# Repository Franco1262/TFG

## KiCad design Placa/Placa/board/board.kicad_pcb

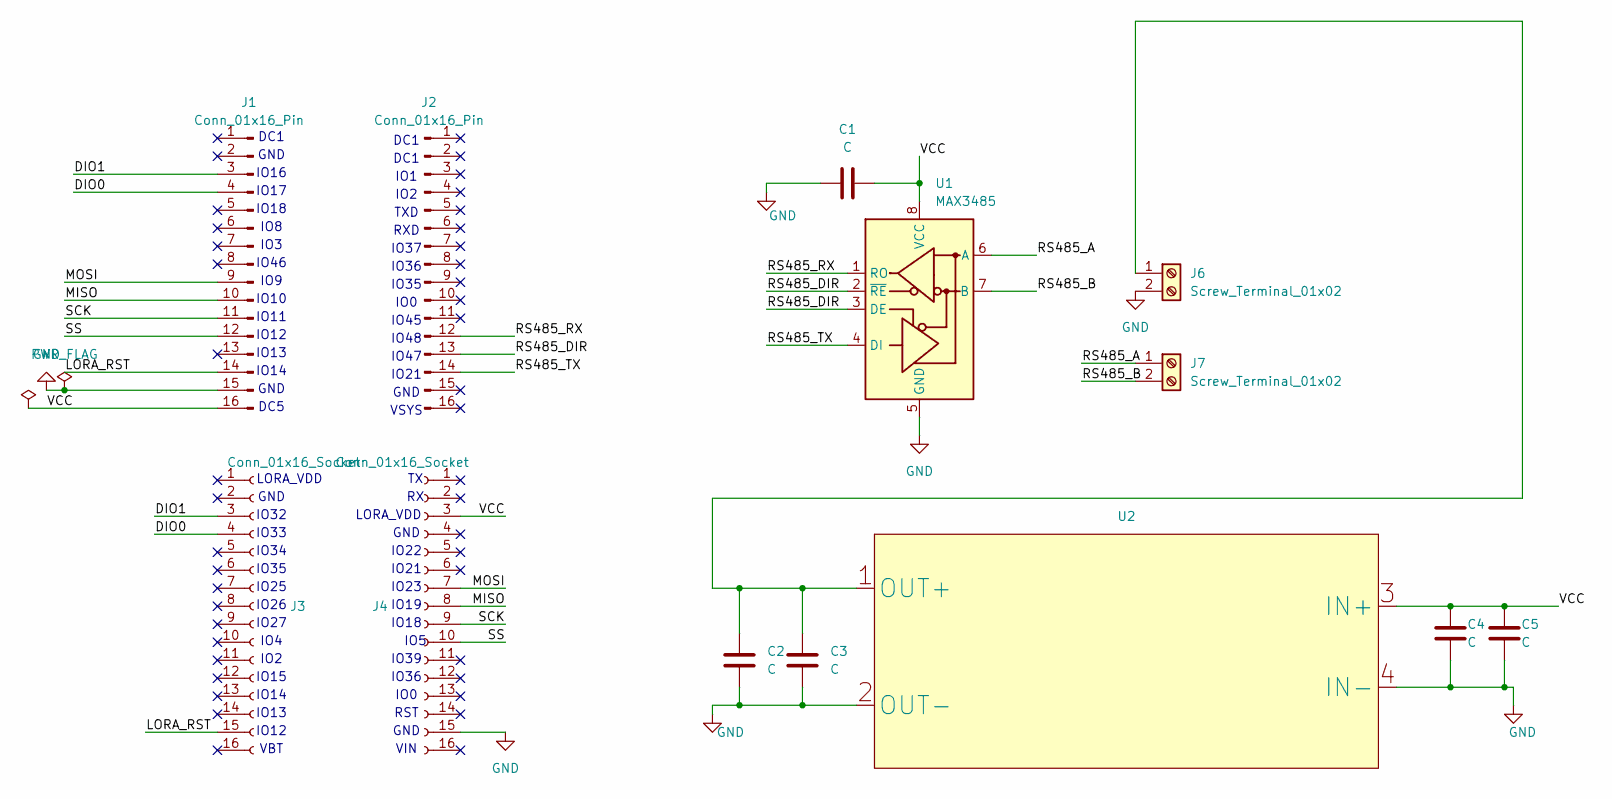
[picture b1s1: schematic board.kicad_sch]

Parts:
C1, C2, C3, C4, C5: C; C_Disc_D5.0mm_W2.5mm_P2.50mm
J1, J2: Conn_01x16_Pin; PinHeader_1x16_P2.54mm_Vertical
J3, J4: Conn_01x16_Socket; PinSocket_1x16_P2.54mm_Vertical
J6, J7: Screw_Terminal_01x02; TerminalBlock_Phoenix_MKDS-1,5-2-5.08_1x02_P5.08mm_Horizont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
U1: MAX3485; DIP-8_W7.62mm
U2: XL6019_Module; Module_XL6019

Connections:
/DIO0: J1.4, J3.4
/DIO1: J1.3, J3.3
/LORA_RST: J1.14, J3.15
/MISO: J1.10, J4.8
/MOSI: J1.9, J4.7
/RS485_A: J7.1, U1.6 (A)
/RS485_B: J7.2, U1.7 (B)
/RS485_DIR: J2.13, U1.2 (~RE), U1.3 (DE)
/RS485_RX: J2.12, U1.1 (RO)
/RS485_TX: J2.14, U1.4 (DI)
/SCK: J1.11, J4.9
/SS: J1.12, J4.10
/VCC: C1.2, C4.2, C5.2, J1.16, J4.3, U1.8 (VCC), U2.3 (IN+)
GND: C1.1, C2.1, C3.1, C4.1, C5.1, J1.15, J4.15, J6.2, U1.5 (GND), U2.2 (OUT-), U2.4 (IN-)
unnamed: C2.2, C3.2, J6.1, U2.1 (OUT+)

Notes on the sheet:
IO2
IO26
RXD
IO13
IO36
RST
IO48
LORA_VDD
GND
IO35
IO32
IO21
IO16
IO17
IO23
DC5
IO18
IO14
IO19
IO5
DC1
IO13
IO9
IO11
VSYS
IO1
IO15
IO34
IO25
GND
IO0
IO12
IO3
IO27
VBT
IO39
TXD
IO37
DC1
IO46

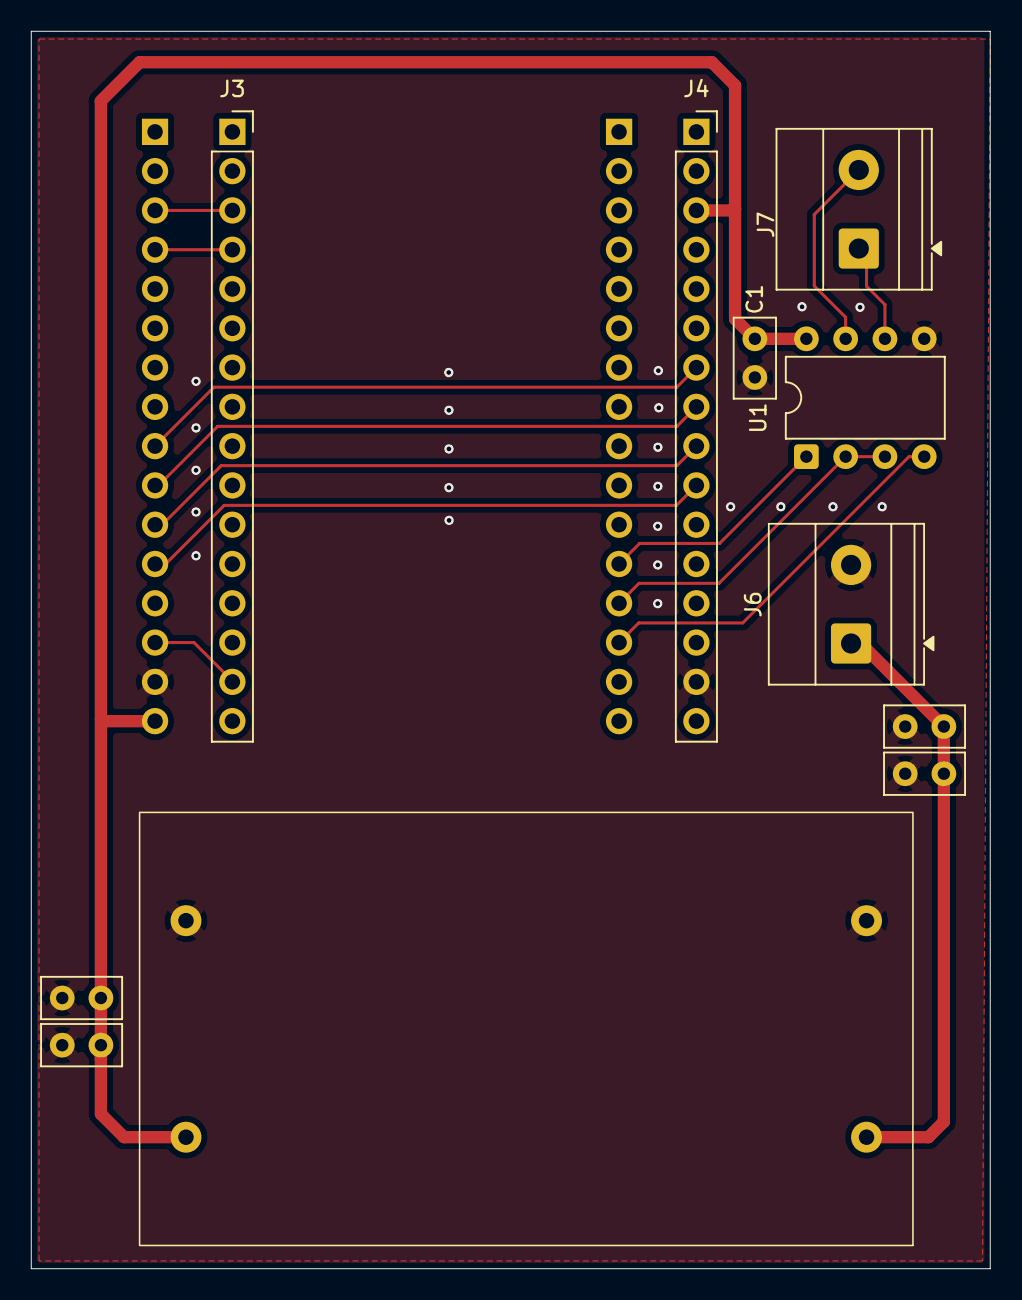
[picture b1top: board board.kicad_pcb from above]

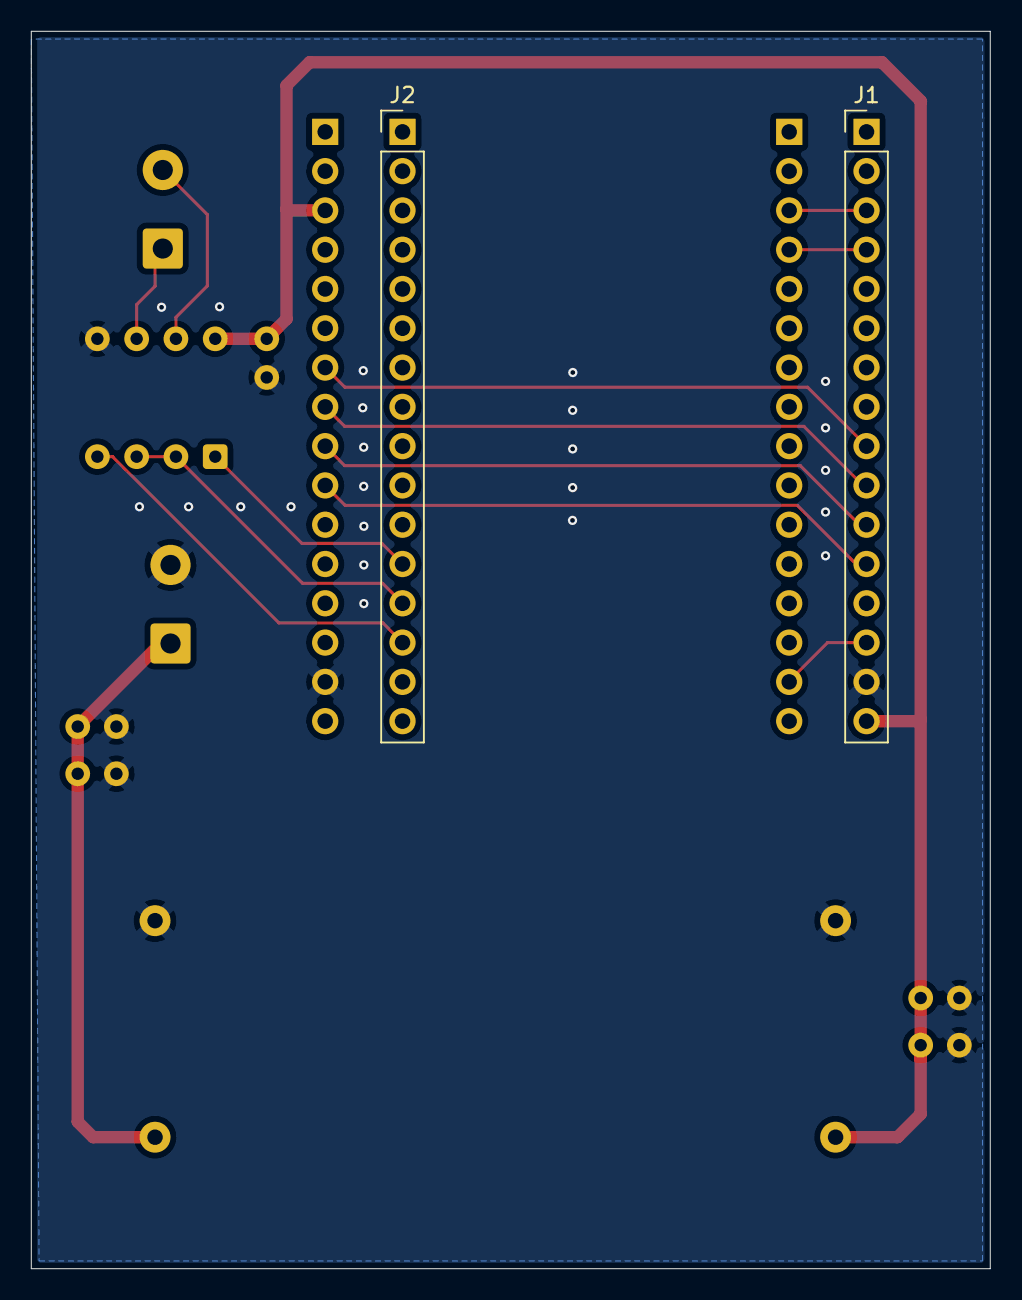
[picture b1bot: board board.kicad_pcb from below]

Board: 2 copper layers, 62.0 x 80.0 mm, 13 parts (2 on the bottom side), 15 nets.

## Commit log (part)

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2025-11-05 Cambios
2025-11-16 Avances
